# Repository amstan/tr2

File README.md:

# tr2

## Overview

The goal of this project is to develop a hardware and accompanying software
platform for controlling robots from a high level programming language such as
Python.

## Hardware

The hardware will consist of a multi-axis motor control board, industrial
strength GPIO for controlling alarms, incandescent lamps, driving fans and more.

## Software

The software will provide an abstract interface to the hardware platform. The
first robot that will be tailored to this project will be a 3-axis Delta Robot.

## Project Structure

Here is the folder structure for the project:

* blender/
    * 3D models of target robots
* board/
    * The first hardware platform for this project
* board/bomParser/
    * Some pretty untested code to do mass changes in schematics/BOMs
* datasheets/
    * Component datasheets
* doc/
    * Notes, logo
* firmware/
    * Bare metal bring up of STM32F4 and code for the robot controller
* pictures/
    * Various pictures of the project
* python/
    * The python software interfaces
* ui/
    * A user interface to all of this

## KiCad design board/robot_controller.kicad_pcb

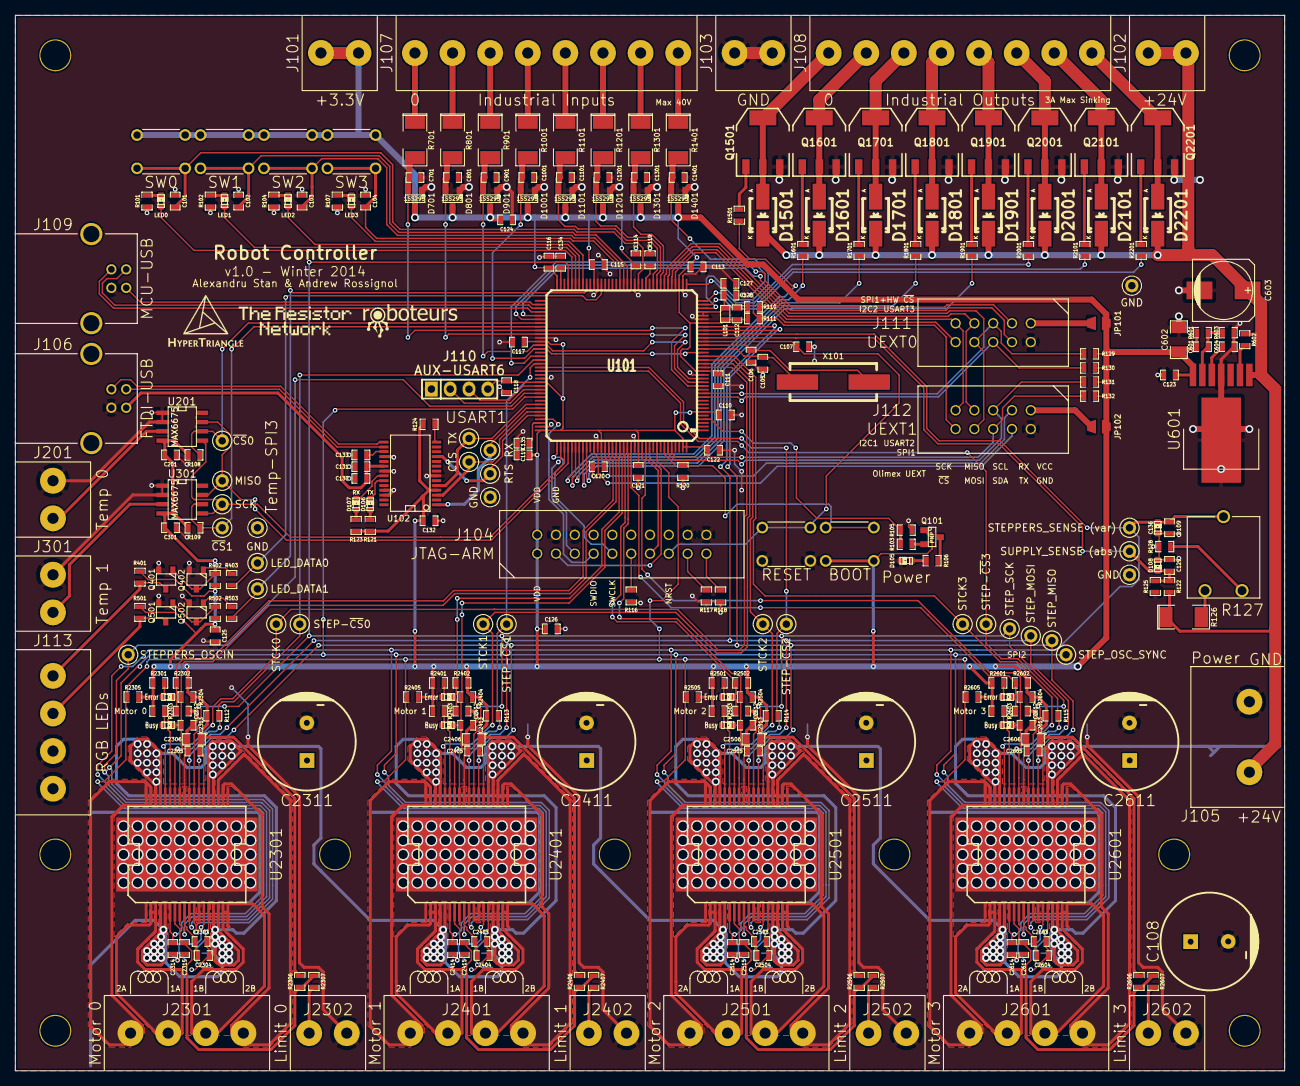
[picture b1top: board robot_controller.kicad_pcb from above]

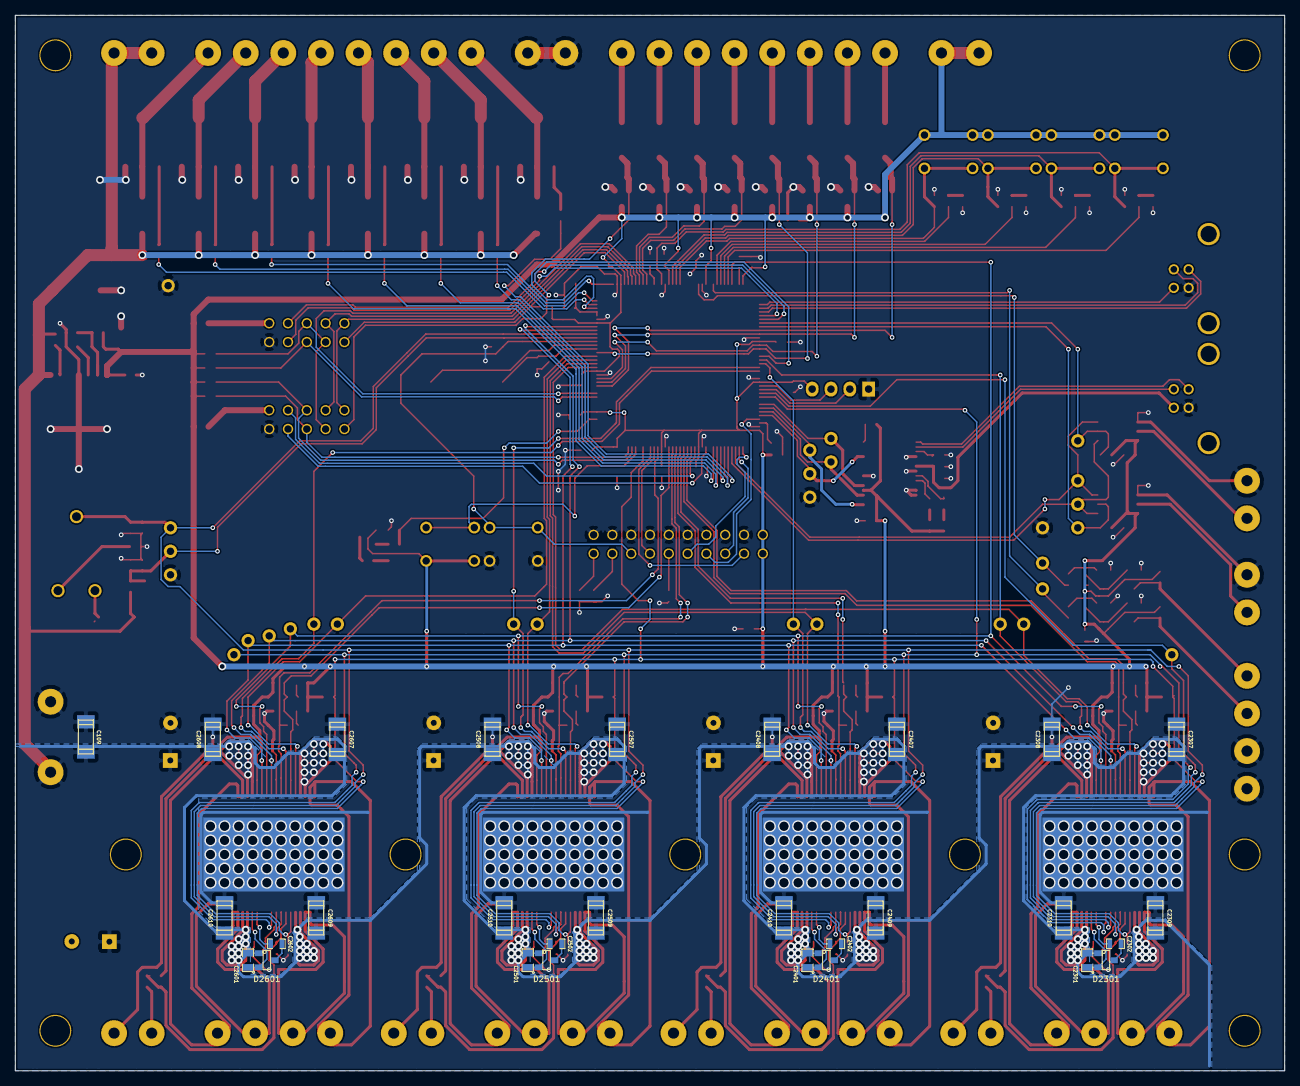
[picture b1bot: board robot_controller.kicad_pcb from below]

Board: 2 copper layers, 171.4 x 142.6 mm, 325 parts (29 on the bottom side), 199 nets.

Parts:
C101, C102, C103, C104, C2304, C2404, C2504, C2604: 10uF; SM0603_Capa
C105, C106: 18pF; SM0603_Capa
C107, C110, C111, C112, C113, C114, C115, C116, C117, C118, C119, C120, C121, C122, C123, C124, C125, C126, C129, C131, C132, C133, C201, C301, C2303, C2305, C2315, C2403, C2405, C2415, C2503, C2505, C2515, C2603, C2605, C2615: 100nF; SM0603_Capa
C108, C2311, C2411, C2511, C2611: 100uF; CP_13x21mm
C109, C2307, C2308, C2309, C2310, C2407, C2408, C2409, C2410, C2507, C2508, C2509, C2510, C2607, C2608, C2609, C2610: 100nF; c_1808
C127: 1uF; SM0603_Capa
C128, C2302, C2402, C2502, C2602: 10nF; SM0603_Capa
C130: 4.7uF; SM0603_Capa
C134, C135: 2.2uF; SM0603_Capa
C136: 33nF; SM0603_Capa
C601, C604: 22nF; SM0603_Capa
C602: 100uF; SM1206
C603: 10uF; c_elec_8x10
C701, C801, C901, C1001, C1101, C1201, C1301, C1401: 1nF; SM0603_Capa
C2301, C2401, C2501, C2601: 220nF; SM0805
C2306, C2406, C2506, C2606: 47uF; SM0805
C2312, C2313, C2314, C2412, C2413, C2414, C2512, C2513, C2514, C2612, C2613, C2614: 100pF; SM0603_Capa
D101: LED0; LED-0603
D102: LED1; LED-0603
D103: LED2; LED-0603
D104: LED3; LED-0603
D105: Power; LED-0603
D106: TX; LED-0603
D107: RX; LED-0603
D108, D109: 3.3V; LED-0603
D701, D801, D901, D1001, D1101, D1201, D1301, D1401: 1SS295; SOT23-EXTRASPECIAL
D1501, D1601, D1701, D1801, D1901, D2001, D2101, D2201: RSX501L-20TE25; Diode-SMA_Handsoldering
D2301, D2401, D2501, D2601: DOUBLE_SCHOTTKY; SOT23-SPECIAL
D2302, D2402, D2502, D2602: Error; LED-0603
D2303, D2403, D2503, D2603: Busy; LED-0603
J101: +3.3V; SCONN_2
J102: +24V; SCONN_2
J103: GND; SCONN_2
J104: JTAG-ARM; SHROUDED_20
J105: Power; PWRSCONN_2
J106: FTDI-USB; USB_B
J107: Industrial Inputs; SCONN_8
J108: Industrial Outputs; SCONN_8
J109: MCU-USB; USB_B
J110: AUX-USART6; Pin_Header_Straight_1x04
J111: UEXT0; SHROUDED_10
J112: UEXT1; SHROUDED_10
J113: RGB LEDs; SCONN_4
J201: Temp 0; SCONN_2
J301: Temp 1; SCONN_2
J2301: Motor 0; CONN_STEPPER
J2302: Limit 0; SCONN_2
J2401: Motor 1; CONN_STEPPER
J2402: Limit 1; SCONN_2
J2501: Motor 2; CONN_STEPPER
J2502: Limit 2; SCONN_2
J2601: Motor 3; CONN_STEPPER
J2602: Limit 3; SCONN_2
JP101, JP102: JUMPER; SOLDER_BRIDGE
L101: 100uH; SM0603
MH: MountingHole_2-5mm_RevA_Date21Jun2010; MountingHole_4mm
MH#2, MH#3, MH#4, MH#5, MH#6, MH#7, MH#8, MH#9: MountingHole_2-5mm_RevA_Date21Jun2010; MountingHole_4mm
Q101: PNP; SOT23-EXTRASPECIAL
Q401, Q402, Q501, Q502: MMBT5962; SOT23_INV
Q1501, Q1601, Q1701, Q1801, Q1901, Q2001, Q2101, Q2201: NJT4031NT1G; SOT223-EXTRASPECIAL
R101, R102, R104, R106, R107, R2307, R2407, R2507, R2607: 100; SM0603_Resistor
R103, R105, R402, R403, R502, R503: 1k; SM0603_Resistor
R108, R109, R110, R111, R112, R113, R114, R115, R116, R117, R118, R119, R120, R124, R2306, R2406, R2506, R2606: 10k; SM0603_Resistor
R121, R2303, R2403, R2503, R2603: 220; SM0603_Resistor
R122: 15k; SM0603_Resistor
R123, R2301, R2401, R2501, R2601: 316; SM0603_Resistor
R125, R603: 1.1k; SM0603_Resistor
R126, R701, R801, R901, R1001, R1101, R1201, R1301, R1401: 3.3k; SM2010
R127: 22k; TRIMMER_POT
R128: 820; SM0603_Resistor
R129, R130, R131, R132: 4.7k; SM0603_Resistor
R401, R501: 200; SM0603_Resistor
R601: 3.3k; SM0603_Resistor
R602: 62k; SM0603_Resistor
R1501, R1601, R1701, R1801, R1901, R2001, R2101, R2201: 470; SM0603_Resistor
R2302, R2304, R2305, R2402, R2404, R2405, R2502, R2504, R2505, R2602, R2604, R2605: 39k; SM0603_Resistor
SW101: SW0; PB
SW102: SW1; PB
SW103: SW2; PB
SW104: SW3; PB
SW105: RESET; PB
SW106: BOOT; PB
TP101: STEP_SCK; MINI_TP
TP102: STEP_MOSI; MINI_TP
TP103: STEP_MISO; MINI_TP
TP104: STEP-~{CS}0; MINI_TP
TP105: STEP-~{CS}1; MINI_TP
TP106: STEP-~{CS}2; MINI_TP
TP107: STEP-~{CS}3; MINI_TP
TP108: STCK0; MINI_TP
TP109: STCK1; MINI_TP
TP110: STCK2; MINI_TP
TP111: STCK3; MINI_TP
TP112: STEPPERS_OSCIN; MINI_TP
TP113: STEP_OSC_SYNC; MINI_TP
TP114, TP115, TP116, TP117: GND; MINI_TP
TP118: RX; MINI_TP
TP119: TX; MINI_TP
TP120: CTS; MINI_TP
TP121: RTS; MINI_TP
TP122: LED_DATA0; MINI_TP
TP123: LED_DATA1; MINI_TP
TP124: MISO; MINI_TP
TP125: SCK; MINI_TP
TP126: ~{CS}0; MINI_TP
TP127: ~{CS}1; MINI_TP
TP128: SUPPLY_SENSE (abs); MINI_TP
TP129: STEPPERS_SENSE (var); MINI_TP
U101: STM32F405-144; TQFP144
U102: FT232RL; SSOP-28
U201, U301: MAX6675; SOIC-8_N
U601: LMZ14201; PFM7
U2301, U2401, U2501, U2601: L6470; POWERSO-36
X101: 8MHZ; Crystal_HC49-SD_SMD

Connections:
+3.3V: C110.1, C111.1, C112.1, C113.1, C114.1, C115.1, C116.1, C117.1, C118.1, C119.1, C120.1, C121.1, C122.1, C123.1, C124.1, C125.1, C126.1, C132.1, C201.1, C301.1, C601.1, C602.1, C2305.1, C2306.1, C2405.1, C2406.1, C2505.1, C2506.1, C2605.1, C2606.1, D701.3, D801.3, D901.3, D1001.3, D1101.3, D1201.3, D1301.3, D1401.3, J101.1, J101.2, J104.1, J104.2, J110.4, JP101.2, JP102.2, L101.1, Q101.1, R108.1, R109.1, R110.1, R111.1, R112.1, R113.1, R114.1, R115.1, R121.2, R123.2, R124.2, R129.1, R130.1, R131.1, R132.1, R401.1, R402.1, R501.1, R502.1, R601.1, R2301.1, R2302.1, R2303.1, R2304.1, R2305.1, R2306.1, R2401.1, R2402.1, R2403.1, R2404.1, R2405.1, R2406.1, R2501.1, R2502.1, R2503.1, R2504.1, R2505.1, R2506.1, R2601.1, R2602.1, R2603.1, R2604.1, R2605.1, R2606.1, SW101.1, SW102.1, SW103.1, SW104.1, SW106.2, U101.6, U101.17, U101.30, U101.39, U101.52, U101.62, U101.72, U101.84, U101.95, U101.108, U101.121, U101.131, U101.143, U101.144, U102.4, U201.4, U301.4, U601.7, U2301.24, U2401.24, U2501.24, U2601.24
+3.3VADC: C127.1, C128.1, L101.2, U101.32, U101.33
+5V: C130.1, C131.1, J106.1, U102.20
+24V: C108.1, C109.1, C603.1, C2301.2, C2307.1, C2308.1, C2309.1, C2310.1, C2311.1, C2401.2, C2407.1, C2408.1, C2409.1, C2410.1, C2411.1, C2501.2, C2507.1, C2508.1, C2509.1, C2510.1, C2511.1, C2601.2, C2607.1, C2608.1, C2609.1, C2610.1, C2611.1, D1501.2, D1601.2, D1701.2, D1801.2, D1901.2, D2001.2, D2101.2, D2201.2, D2301.1, D2401.1, D2501.1, D2601.1, J102.1, J102.2, J105.1, R122.1, R126.1, R602.1, U601.1, U2301.4, U2301.5, U2301.15, U2301.16, U2301.22, U2301.23, U2301.33, U2301.34, U2401.4, U2401.5, U2401.15, U2401.16, U2401.22, U2401.23, U2401.33, U2401.34, U2501.4, U2501.5, U2501.15, U2501.16, U2501.22, U2501.23, U2501.33, U2501.34, U2601.4, U2601.5, U2601.15, U2601.16, U2601.22, U2601.23, U2601.33, U2601.34
/BOOT0: R120.1, SW106.1, U101.138
/BOOT1: R119.1, U101.48
/I2C1_SCL: J112.5, R131.2, U101.139
/I2C1_SDA: J112.6, R132.2, U101.140
/I2C2_SCL: J111.5, R129.2, U101.11
/I2C2_SDA: J111.6, R130.2, U101.10
/Industrial Input 0/A/D_Input: J107.1, R701.1
/Industrial Input 0/MCU_Input: C701.1, D701.2, R701.2, U101.13, U101.81
/Industrial Input 1/A/D_Input: J107.2, R801.1
/Industrial Input 1/MCU_Input: C801.1, D801.2, R801.2, U101.14, U101.82
/Industrial Input 2/A/D_Input: J107.3, R901.1
/Industrial Input 2/MCU_Input: C901.1, D901.2, R901.2, U101.15, U101.85
/Industrial Input 3/A/D_Input: J107.4, R1001.1
/Industrial Input 3/MCU_Input: C1001.1, D1001.2, R1001.2, U101.22, U101.86
/Industrial Input 4/A/D_Input: J107.5, R1101.1
/Industrial Input 4/MCU_Input: C1101.1, D1101.2, R1101.2, U101.46
/Industrial Input 5/A/D_Input: J107.6, R1201.1
/Industrial Input 5/MCU_Input: C1201.1, D1201.2, R1201.2, U101.45
/Industrial Input 6/A/D_Input: J107.7, R1301.1
/Industrial Input 6/MCU_Input: C1301.1, D1301.2, R1301.2, U101.44
/Industrial Input 7/A/D_Input: J107.8, R1401.1
/Industrial Input 7/MCU_Input: C1401.1, D1401.2, R1401.2, U101.34
/Industrial Output 0/MCU_Pin: R1501.1, U101.113
/Industrial Output 0/Sink: D1501.1, J108.1, Q1501.3
/Industrial Output 1/MCU_Pin: R1601.1, U101.114
/Industrial Output 1/Sink: D1601.1, J108.2, Q1601.3
/Industrial Output 2/MCU_Pin: R1701.1, U101.115
/Industrial Output 2/Sink: D1701.1, J108.3, Q1701.3
/Industrial Output 3/MCU_Pin: R1801.1, U101.116
/Industrial Output 3/Sink: D1801.1, J108.4, Q1801.3
/Industrial Output 4/MCU_Pin: R1901.1, U101.117
/Industrial Output 4/Sink: D1901.1, J108.5, Q1901.3
/Industrial Output 5/MCU_Pin: R2001.1, U101.37
/Industrial Output 5/Sink: D2001.1, J108.6, Q2001.3
/Industrial Output 6/MCU_Pin: R2101.1, U101.36
/Industrial Output 6/Sink: D2101.1, J108.7, Q2101.3
/Industrial Output 7/MCU_Pin: R2201.1, U101.35
/Industrial Output 7/Sink: D2201.1, J108.8, Q2201.3
/JTCK/SWCLK: J104.9, U101.109
/JTDI: J104.5, U101.110
/JTDO: J104.13, U101.133
/JTMS/SWDIO: J104.7, U101.105
/LED0: D101.1, U101.68
/LED1: D102.1, U101.67
/LED2: D103.1, U101.66
/LED3: D104.1, U101.65
/LED Data 0/DATA_IN: R403.2, TP122.1, U101.60
/LED Data 0/DATA_OUT: J113.1, Q401.3, R401.2
/LED Data 1/DATA_IN: R503.2, TP123.1, U101.64
/LED Data 1/DATA_OUT: J113.2, Q501.3, R501.2
/LED_PWR: R103.1, R105.2, U101.4
/MCU_RESET: C107.1, J104.15, SW105.1, U101.25
/NJTRST: J104.3, U101.134
/SPI1_MISO: J111.7, J112.7, U101.42
/SPI1_MOSI: J111.8, J112.8, U101.43
/SPI1_SCK: J111.9, J112.9, U101.41
/SUPPLY_SENSE: C129.1, D108.2, R122.2, R125.1, TP128.1, U101.26
/SW0: C101.1, SW101.2, U101.50
/SW1: C102.1, SW102.2, U101.53
/SW2: C103.1, SW103.2, U101.54
/SW3: C104.1, SW104.2, U101.55
/Stepper 0/ADCIN: C136.1, D109.2, R127.2, TP129.1, U101.27, U2301.8, U2401.8, U2501.8, U2601.8
/Stepper 0/OSCIN: TP112.1, U101.98, U2301.10
/Stepper 0/SCK: TP101.1, U101.69, U2301.26, U2401.26, U2501.26, U2601.26
/Stepper 0/SDI: TP102.1, U101.29, U2301.27, U2401.27, U2501.27, U2601.27
/Stepper 0/SDO: TP103.1, U101.28, U2301.25, U2401.25, U2501.25, U2601.25
/Stepper 0/STCK: TP108.1, U101.18, U2301.32
/Stepper 0/VREG: C2303.1, C2304.1, U2301.9
/Stepper 0/~BUSY/SYNC: C2313.1, D2303.2, R2304.2, U101.124, U2301.29
/Stepper 0/~CS: R112.2, TP104.1, U101.89, U2301.30
/Stepper 0/~FLAG: C2312.1, D2302.2, R2302.2, U101.123, U2301.31
/Stepper 0/~STBY/RST: C2314.1, C2414.1, C2514.1, C2614.1, R2305.2, R2405.2, R2505.2, R2605.2, U101.136, U2301.6, U2401.6, U2501.6, U2601.6
/Stepper 1/OSCIN: TP113.1, U101.99, U2301.11, U2401.10, U2501.10, U2601.10
/Stepper 1/STCK: TP109.1, U101.19, U2401.32
/Stepper 1/VREG: C2403.1, C2404.1, U2401.9
/Stepper 1/~BUSY/SYNC: C2413.1, D2403.2, R2404.2, U101.126, U2401.29
/Stepper 1/~CS: R113.2, TP105.1, U101.90, U2401.30
/Stepper 1/~FLAG: C2412.1, D2402.2, R2402.2, U101.125, U2401.31
/Stepper 2/STCK: TP110.1, U101.20, U2501.32
/Stepper 2/VREG: C2503.1, C2504.1, U2501.9
/Stepper 2/~BUSY/SYNC: C2513.1, D2503.2, R2504.2, U101.128, U2501.29
/Stepper 2/~CS: R114.2, TP106.1, U101.91, U2501.30
/Stepper 2/~FLAG: C2512.1, D2502.2, R2502.2, U101.127, U2501.31
/Stepper 3/STCK: TP111.1, U101.21, U2601.32
/Stepper 3/VREG: C2603.1, C2604.1, U2601.9
/Stepper 3/~BUSY/SYNC: C2613.1, D2603.2, R2604.2, U101.132, U2601.29
/Stepper 3/~CS: R115.2, TP107.1, U101.92, U2601.30
/Stepper 3/~FLAG: C2612.1, D2602.2, R2602.2, U101.129, U2601.31
/Temp Sensor 0/SCK: TP125.1, U101.111, U201.5, U301.5
/Temp Sensor 0/SO: TP124.1, U101.112, U201.7, U301.7
/Temp Sensor 0/~CS: R108.2, TP126.1, U101.79, U201.6
/Temp Sensor 1/~CS: R109.2, TP127.1, U101.80, U301.6
/UEXT0_~CS: J111.10, R110.2, U101.40
/UEXT1_~CS: J112.10, R111.2, U101.88
/USART1_CTS: TP120.1, U101.103, U102.3
/USART1_RTS: TP121.1, U101.104, U102.11
/USART1_RX: TP118.1, U101.102, U102.1
/USART1_TX: TP119.1, U101.101, U102.5
/USART2_RX: J112.3, U101.122
/USART2_TX: J112.4, U101.119
/USART3_RX: J111.3, U101.78
/USART3_TX: J111.4, U101.77
/USART6_RX: J110.2, U101.97
/USART6_TX: J110.3, U101.96
/USB_DM: J109.2, U101.75
/USB_DP: J109.3, U101.76
/USB_VBUS: J109.1, U101.74
/VCAP1: C134.1, U101.71
/VCAP2: C135.1, U101.106
/XTAL_IN: C105.1, U101.23, X101.1
/XTAL_OUT: C106.1, U101.24, X101.2
GND: C101.2, C102.2, C103.2, C104.2, C105.2, C106.2, C107.2, C108.2, C109.2, C110.2, C111.2, C112.2, C113.2, C114.2, C115.2, C116.2, C117.2, C118.2, C119.2, C120.2, C121.2, C122.2, C123.2, C124.2, C125.2, C126.2, C127.2, C128.2, C129.2, C130.2, C131.2, C132.2, C133.2, C134.2, C135.2, C136.2, C201.2, C301.2, C602.2, C603.2, C604.2, C701.2, C801.2, C901.2, C1001.2, C1101.2, C1201.2, C1301.2, C1401.2, C2303.2, C2304.2, C2305.2, C2306.2, C2307.2, C2308.2, C2309.2, C2310.2, C2311.2, C2312.2, C2313.2, C2314.2, C2315.2, C2403.2, C2404.2, C2405.2, C2406.2, C2407.2, C2408.2, C2409.2, C2410.2, C2411.2, C2412.2, C2413.2, C2414.2, C2415.2, C2503.2, C2504.2, C2505.2, C2506.2, C2507.2, C2508.2, C2509.2, C2510.2, C2511.2, C2512.2, C2513.2, C2514.2, C2515.2, C2603.2, C2604.2, C2605.2, C2606.2, C2607.2, C2608.2, C2609.2, C2610.2, C2611.2, C2612.2, C2613.2, C2614.2, C2615.2, D105.2, D108.1, D109.1, D701.1, D801.1, D901.1, D1001.1, D1101.1, D1201.1, D1301.1, D1401.1, J103.1, J103.2, J104.4, J104.6, J104.8, J104.10, J104.12, J104.14, J104.16, J104.18, J104.20, J105.2, J106.4, J109.4, J110.1, J111.2, J112.2, J113.3, J113.4, J201.1, J301.1, J2302.2, J2402.2, J2502.2, J2602.2, Q401.1, Q402.1, Q501.1, Q502.1, Q1501.1, Q1601.1, Q1701.1, Q1801.1, Q1901.1, Q2001.1, Q2101.1, Q2201.1, R101.2, R102.2, R104.2, R105.1, R107.2, R116.2, R117.2, R118.2, R119.2, R120.2, R125.2, R128.2, R603.2, SW105.2, TP114.1, TP115.1, TP116.1, TP117.1, U101.16, U101.31, U101.38, U101.51, U101.61, U101.83, U101.94, U101.107, U101.120, U101.130, U102.7, U102.18, U102.21, U102.25, U102.26, U201.1, U201.2, U301.1, U301.2, U601.4, U2301.1, U2301.12, U2301.19, U2301.28, U2301.PAD, U2401.1, U2401.12, U2401.19, U2401.28, U2401.PAD, U2501.1, U2501.12, U2501.19, U2501.28, U2501.PAD, U2601.1, U2601.12, U2601.19, U2601.28, U2601.PAD
unnamed: C133.1, U102.17
unnamed: C601.2, R601.2, R603.1, U601.6
unnamed: C604.1, U601.5
unnamed: C2301.1, D2301.3, U2301.14
unnamed: C2302.1, D2301.2
unnamed: C2302.2, U2301.13
unnamed: C2315.1, R2306.2, R2307.2, U2301.7
unnamed: C2401.1, D2401.3, U2401.14
unnamed: C2402.1, D2401.2
unnamed: C2402.2, U2401.13
unnamed: C2415.1, R2406.2, R2407.2, U2401.7
unnamed: C2501.1, D2501.3, U2501.14
unnamed: C2502.1, D2501.2
unnamed: C2502.2, U2501.13
unnamed: C2515.1, R2506.2, R2507.2, U2501.7
unnamed: C2601.1, D2601.3, U2601.14
unnamed: C2602.1, D2601.2
unnamed: C2602.2, U2601.13
unnamed: C2615.1, R2606.2, R2607.2, U2601.7
unnamed: D101.2, R101.1
unnamed: D102.2, R102.1
unnamed: D103.2, R104.1
unnamed: D104.2, R107.1
unnamed: D105.1, R106.1
unnamed: D106.1, R121.1
unnamed: D106.2, U102.23
unnamed: D107.1, R123.1
unnamed: D107.2, U102.22
unnamed: D2302.1, R2301.2
unnamed: D2303.1, R2303.2
unnamed: D2402.1, R2401.2
unnamed: D2403.1, R2403.2
unnamed: D2502.1, R2501.2
unnamed: D2503.1, R2503.2
unnamed: D2602.1, R2601.2
unnamed: D2603.1, R2603.2
unnamed: J104.11, R116.1
unnamed: J104.17, R117.1
unnamed: J104.19, R118.1
unnamed: J106.2, U102.16
unnamed: J106.3, U102.15
unnamed: J111.1, JP101.1
unnamed: J112.1, JP102.1
unnamed: J201.2, U201.3
unnamed: J301.2, U301.3
unnamed: J2301.1, U2301.35, U2301.36
unnamed: J2301.2, U2301.2, U2301.3
unnamed: J2301.3, U2301.17, U2301.18
unnamed: J2301.4, U2301.20, U2301.21
unnamed: J2302.1, R2307.1
unnamed: J2401.1, U2401.35, U2401.36
unnamed: J2401.2, U2401.2, U2401.3
unnamed: J2401.3, U2401.17, U2401.18
unnamed: J2401.4, U2401.20, U2401.21
unnamed: J2402.1, R2407.1
unnamed: J2501.1, U2501.35, U2501.36
unnamed: J2501.2, U2501.2, U2501.3
unnamed: J2501.3, U2501.17, U2501.18
unnamed: J2501.4, U2501.20, U2501.21
unnamed: J2502.1, R2507.1
unnamed: J2601.1, U2601.35, U2601.36
unnamed: J2601.2, U2601.2, U2601.3
unnamed: J2601.3, U2601.17, U2601.18
unnamed: J2601.4, U2601.20, U2601.21
unnamed: J2602.1, R2607.1
unnamed: Q101.2, R103.2
unnamed: Q101.3, R106.2
unnamed: Q401.2, Q402.3, R402.2
unnamed: Q402.2, R403.1
unnamed: Q501.2, Q502.3, R502.2
unnamed: Q502.2, R503.1
unnamed: Q1501.2, R1501.2
unnamed: Q1601.2, R1601.2
unnamed: Q1701.2, R1701.2
unnamed: Q1801.2, R1801.2
unnamed: Q1901.2, R1901.2
unnamed: Q2001.2, R2001.2
unnamed: Q2101.2, R2101.2
unnamed: Q2201.2, R2201.2
unnamed: R124.1, U102.14
unnamed: R126.2, R127.1
unnamed: R127.3, R128.1
unnamed: R602.2, U601.2

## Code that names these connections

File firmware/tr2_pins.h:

#pragma once

#define _JOINPIN(port, pin) port##_##pin

// USB
#define USB_VBUS PB13
#define USB_DM   PB14 // not a bootloader D:
#define USB_DP   PB15

// FTDI
#define FTDI_USART(x) _JOINPIN(USART1, x) // + bootloader
#define USART1_TX  PA9
#define USART1_RX  PA10
#define USART1_CTS PA11
#define USART1_RTS PA12

// AUX_UART
#define AUX_USART(x) _JOINPIN(USART6, x)
#define USART6_TX PC6
#define USART6_RX PC7

// UEXT0
#define UEXT0_USART(x) _JOINPIN(USART3, x)
#define USART3_TX PD8
#define USART3_RX PD9

#define UEXT0_I2C(x) _JOINPIN(I2C2, x) // 4.7k pullups
#define I2C2_SDA  PF0
#define I2C2_SCL  PF1

#define UEXT0_SPI(x) _JOINPIN(SPI1, x) // Same as UEXT1
#define UEXT0_CS  PA4

// UEXT1
#define UEXT1_USART(x) _JOINPIN(USART2, x)
#define USART2_TX PD5
#define USART2_RX PD6

#define UEXT1_I2C(x) _JOINPIN(I2C1, x) // 4.7k pullups
#define I2C1_SDA  PB9
#define I2C1_SCL  PB8

#define UEXT1_SPI(x) _JOINPIN(SPI1, x) // Same as UEXT0
#define UEXT1_CS  PA4

#define SPI1_MOSI PA7
#define SPI1_MISO PA6
#define SPI1_SCK  PA5

// Misc
#define BOOT1 PB2 // 10k ext pulldown

#define NJTRST PB4
#define JTDI   PA15
#define JTMS   PA13
#define JTCK   PA14
#define JTDO   PB3

#define XTAL_IN  PH0
#define XTAL_OUT PH1

// RGB LED connectors
#define LED_DATA0 PE9
#define LED_DATA1 PE11
// Note: need rework to bypass broken "booster"

// Board LEDs
#define LED_PWR PE5 // Active low, HiZ also means on

#define LED0 PE15 // Active high
#define LED1 PE14
#define LED2 PE13
#define LED3 PE12

// Board Buttons, 10uF, need software pulldowns
#define SW0 PF12
#define SW1 PF13
#define SW2 PF14
#define SW3 PF15

// Analog
#define SUPPLY_SENSE   PC0 // ADC123_IN10, 1.1k / (1.1k + 15k) * 24V
#define STEPPERS_SENSE PC1 // ADC123,IN11, Settable potentiometer, ideally at 0.5 * 3.3V, goes to ADCIN on L6470

// Industrial Inputs
// 48kHz Single Pole Low Pass Filter (3.3k, 1nF)
// 0.7mA @ 24V Input, 210mV drop on Schottky array
// Max 40V
#define IND_INPUT0 PF3  // ADC3_IN9
#define IND_INPUT1 PF4  // ADC3_IN14
#define IND_INPUT2 PF5  // ADC3_IN15
#define IND_INPUT3 PF10 // ADC3_IN8
#define IND_INPUT4 PB0  // ADC12_IN8
#define IND_INPUT5 PC5  // ADC12_IN15
#define IND_INPUT6 PC4  // ADC12_IN14
#define IND_INPUT7 PA0  // ADC123_IN0
#define IND_INPUT0_TIM PD12
#define IND_INPUT1_TIM PD13
#define IND_INPUT2_TIM PD14
#define IND_INPUT3_TIM PD15

// Industrial Outputs
// 3A Max Sinking
// NJT4031NT1G NPN transistors + flyback diodes to 24V
#define IND_OUTPUT0 PC12
#define IND_OUTPUT1 PD0
#define IND_OUTPUT2 PD1
#define IND_OUTPUT3 PD2
#define IND_OUTPUT4 PD3
#define IND_OUTPUT5 PA3
#define IND_OUTPUT6 PA2
#define IND_OUTPUT7 PA1

// MAX6675
#define TEMP_SPI(x)  _JOINPIN(SPI3, x)
#define SPI3_MISO PC11
#define SPI3_SCK  PC10
#define TEMP0_CS  PD10
#define TEMP1_CS  PD11

// L6470 Steppers
#define STEPPERS_RST      PB6
#define STEPPERS_OSCIN    PC8
#define STEPPERS_OSC_SYNC PC9

#define STEPPERS_SPI(x) _JOINPIN(SPI2, x)
#define SPI2_MOSI PC3
#define SPI2_MISO PC2
#define SPI2_SCK  PB10

#define STEPPER0_CS PG4
#define STEPPER1_CS PG5
#define STEPPER2_CS PG6
#define STEPPER3_CS PG7

#define STEPPER0_STCK PF6
#define STEPPER1_STCK PF7
#define STEPPER2_STCK PF8
#define STEPPER3_STCK PF9

#define STEPPER0_FLAG PD7 // Error when low
#define STEPPER1_FLAG PG10
#define STEPPER2_FLAG PG12
#define STEPPER3_FLAG PG14

#define STEPPER0_BUSY PG9 // !BUSY/FLAG
#define STEPPER1_BUSY PG11
#define STEPPER2_BUSY PG13
#define STEPPER3_BUSY PG15

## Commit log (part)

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2013-10-02 Initial commit: readme and python gitignore
2013-10-03 added folders
2013-10-03 start of kinematics code: some forward kinematics math
2013-10-05 rotated blender model so it matches the code
2013-10-05 Got blender to do live inverse kinematics using our code. Changed to the right point for the circle intersect
2013-10-06 fixed forward kinematics(i had the radius wrong), blender can now do forward kinematics too
2013-10-06 Tried to see how the the resolution distribution looks like.
2013-12-09 Updated README, Renamed board-1 folder
    I have updated the README file to contain a bit more details about the
    project. I have renamed the pcb/ folder to board-1/. I anticipate that
    this project could support multiple hardware platforms.
2013-12-11 organized python folder
2014-01-05 added a virtual stepper driver attempt
2014-01-05 finally made the stepper code compatible with python3, freaking bytes and unicode!
2014-01-14 stops in time now, for all positive cases!
2014-01-14 perfect moving
2014-01-21 Created a KiCAD project
    This commit brings in a KiCAD project that is empty. I am preparing to
    build the latest version of KiCAD.
2014-01-22 organized datasheets in their own folders
2014-01-22 Created STM32F405-144 Component in Project Library
2014-01-25 Added Stepper Motor Driver(L670)
2014-01-25 Added watercooling drawing
2014-01-26 Added MAX6675 symbol to the components library. Fixed pins on L6470.
2014-01-27 Voltage Regulator, Reset Logic
2014-01-27 Added schematic for the temperature amplifier. Removed useless NC pin.
2014-01-27 Wired up the stepper driver blocks in the main schematic.
2014-01-27 Fixed airwire positions.
2014-01-27 Industrial Input
    I have designed an industrial input that is low-pass filtered and
    schottky diode protected against over and under voltage. This circuit
    will work for both analog and digital.
2014-01-27 Industrial Input Schematic Notes
2014-01-29 Worked on the stepper motor interface.
    * Organized stepper files better(moved buspirate driver in another file).
    * Added check for the status register(with exceptions!).
    * Tried the bigger motor(no OCD problems this time!).
2014-01-30 Played some more with the servo settings.
    I can now run the servo at almost the full speed allowed by the driver(1048575).
    At this speed the motor uses almost the full 3A.
2014-02-01 Robot Controller Boot Logic, Decoupling
    I have added boot logic to the main schematic that will allow us to
    boot from the serial bootloader by pressing a button on the board.
    I have added decoupling to the base MCU for analog and digital.
2014-02-01 Hardware USB
    I have added hardware USB support to the board.
2014-02-01 SPI for Steppers and Temperature
    I cleaned up the stepper driver section of the main schematic and
    routed the high speed SPI interface over to it. I also got the second
    SPI module connected to the temperature sensors.
2014-02-01 Added JTAG Debug Port
    I have added the JTAG debug port. The JTAG lines are internally pulled
    high by the MCU to avoid an unknown JTAG state.
2014-02-02 switched to pirate430 driver, added some safety when resetting
2014-02-02 Removed double schottky
    The double schottky wouldn't do much in this case. I have removed it.
2014-02-06 Schematic Additions
    * UEXT
    * AUX UART
    * Regulator
    * Fixed hirearchical label directions
2014-02-06 Decoupled analog section with an inductor.
2014-02-06 Replaces the 2 diodes with a double shottky diode for the steppers.
2014-02-06 Connected USB VBUS to the right MCU pin.
2014-02-06 Connected the UEXT UARTS/I2C/SPI in the right places
2014-02-07 Created Firmware README
2014-02-08 OpenOCD in the Makefile, Simple main program!
    I got OpenOCD going in the Makefile and wrote a simple while(1) test program. I
    was able to load it using gdb 'load'. Woo!
2014-02-08 Default interrupt handler
    Added a default interrupt handler. The chip just goes into it, I need
    to figure that out.
2014-02-08 Blue LED!
    This commit enables the blue LED on the STM32F4DISCOVERY board.
2014-02-08 Simplistic Reset/Clock, Gpio Drivers
    This commit brings in the foundation for a driver for the reset/clock
    logic and gpio peripherals.
2014-02-09 GPIO Headers Complete
    I have finished the GPIO header file. It would be nice to write some
    driver functions, but this is good enough for now.
2014-02-09 GPIO Headers, Peripherals Added to Clock Driver
    I have mostly completed the GPIO headers. I have added the remaining
    peripherals to the SystemResetClock header. I think it is time for an
    SPI driver.
2014-02-09 Things are getting a little volatile!
    Silly me.. forgot to make struct instances volatile. Compiler
    optimizations were sure to break my sample programs.
2014-02-10 Reiner Documentation, Industrial GPIO, Driver Fix
    I added documentation for the meaning of Reiner's board pins. I have
    finished implemented the industrial inputs on the schematic and partial
    industrial outputs. I have added some capacitors to the motor drivers.
2014-02-10 GPIO Update, Spi Update, Uart Started
    I have changed GPIO to be a struct of GPIO modules, removed the enum
    of SPI modules and started working on the UART.
2014-02-12 Made a more efficient use of the MCU hardware peripherals.
    See https://github.com/amstan/tr2/wiki/MCU-Pheripherals-Allocation for more details.
    * Added STCK pins to individual timers so the MCU can control the steppers step by step.
    * Worried about the Industrial GPIOs to be connected to timers(most of them)
    * Swapped some SPIs and UARTs to achieve better speeds
    * Cleaned up schematic
2014-02-13 Added fp-lib-table and a library with an existing stepper motor package
2014-02-15 UART Working, Interrupts
    UART is now working, I am able to transmit bytes. I have wrote a header
    file for the NVIC in the Cortex-M4 core. It needs a bit of work, but I
    am able to enable the UART interrupt and execute it.
2014-02-15 Added POWERSO-36 footprint
2014-02-16 Added test points to the schematic.
2014-02-16 Comprehensive Schematic Review, Power LED
    The schematic was reviewed. Components were selected. Fixed minor bugs
    encountered during review. Debounced switches.
    Added a power LED with a transistor that causes it to be normally-on.
2014-02-16 Fixed ERC Errors. Annotated all components.
2014-02-16 GDB Init, Interrupts, Start Code in C, UART Start
    * Created a GDB init file that automatically connects to OpenOCD
    and reset/halts the processor
    * Wrote a header file for the NVIC in the M4
    * Changed start code to C, found some bugs in the asm version (I suck
    at assembly).
    * Started working on an interrupt driven UART driver
2014-02-16 Renamed Registers to enumerated types
    I have renamed the register bit names to enumerated types if
    applicable. This makes debugging a bit nicer.
2014-02-16 Interrupt Driven Tx and Rx
    I have interrupt driven, non-blocking Tx and Rx working now. I need to
    concern myself with thread safety now before saying this is complete.
2014-02-17 Selected Part Numbers for all Components
2014-02-17 Thread Safety Bug Fixes
    I have made the driver thread-safe by disabling Tx/Rx interrupts when
    accessing the Tx and Rx buffers.
2014-02-17 Industrial Output Ground, Associated Footprints
    * Fixed an issue with the industrial output ground, it is now on the
    power ground rail.
    * Associated most of the footprints, need to make a few.
2014-02-17 Resolved issues while associating footprints.
2014-02-17 Pin/Port GPIO Definitions, Typedef'd GPIO Structs
2014-02-17 Added a Pins Enum, Changed Sample Program to Echo
2014-02-17 Digikey Link Adder
    I have created a utility to interactively add Digikey part numbers and
    links to our schematics. This will help a lot when creating footprints
    and placing orders.
2014-02-17 Minor tweaks to the Digikey Link Adder Regex
2014-02-17 Created Stepper Driver Footprint, FreeCAD Test
    I created a stepper driver footprint.
    I also experimented with FreeCAD in the models folder. It might be nice
    to create 3D models of our components.
2014-02-17 Renamed Clocks
    I renamed the clock define.
2014-02-18 Prepared components/footprints for PCB Layout.
2014-02-19 Worked a little on the PCB layout.
2014-02-20 Worked on the stepper layout
2014-02-28 PFM7 Footprint
    Created a footprint for the TI PFM7 package. Used for the main 3.3V
    switching regulator.
2014-02-28 SOT223 Extra Special
    Created SOT223 package for the industrial output transistors.
2014-02-28 Added vias of proper sizes for 24V near the stepper drivers
2014-03-01 Worked on a way to route the 5 wires underneath the capacitor.
2014-03-01 SCONN_8 Footprint
    Created SCONN_8 footprint for the industrial GPIO.
2014-03-01 Started layout of a few other 'modules'. More work on the stepper drivers. Used more Andrew footprints.
2014-03-01 USB_B Footprint
    Created a USB-B connector footprint.
2014-03-02 TRIMMER_POT Footprint
    Created a trim pot footprint.
2014-03-02 Layed out in general where stuff is going to be located.
2014-03-02 Organized MCU components in the layout
2014-03-02 MINI_TP Footprint
    Created a footprint for the test points used in our project.
2014-03-02 Added pushbuttons to the PCB Layout
2014-03-02 SOLDER_BRIDGE Footprint
    Added the SOLDER_BRIDGE footprint to our component library. I added it
    to the layout as well.
2014-03-02 Named all connectors/leds/switches based on their functionality, refdes's are safe.
2014-03-02 Copied stepper layouts, no extra parts were found :)
2014-03-03 Added more zones. Started routing traces from stepper motors
2014-03-08 Started layout on the mcu.
2014-03-10 More pcb layout
2014-03-10 No more airwires
2014-03-10 Board pretty much done.
2014-03-10 Fixed Main Power Footprint
    Updated the footprint on the PCB layout and the track connected to it.
2014-03-10 moved board to fit in the page
2014-03-10 Fixed hole size on shrouded connectors
2014-03-10 Increased the size of the PFM heatsink.
    Solder can be applied from the top now, hopefully avoiding an oven.
2014-03-10 Fixed DRC with the new part changes
2014-03-11 More silkscreen changes, more track fiddling.
2014-03-11 PentaLogix DRC Fixes
    Moved some traces inside of the board outline.
2014-03-11 Fixed annular ring errors
2014-03-11 Removed soldermask from the bottom side of the board underneath the drivers.
2014-03-14 SPI WriteRead Function
2014-03-15 Initial UI Work
    Started creating a user interface.
2014-03-15 Pictures taken before PCB assembly
    Taken with a small USB microscope.
2014-03-15 Updated README, Started Protocol Definition
2014-03-15 User LED protocol definition
2014-03-24 Moved board stuff in the board folder
2014-03-25 Struct to Defines
    I changed from a struct with padding variables to multiple UART
    defines. The padding variables do not make much sense.
    Protocol definition is under way.
2014-03-26 Continued Protocol Definition
2014-03-27 Stepper Driver Improvements
    Added better exception handling.
    It now includes descriptions for the exceptions and __str__ and __repr__ methods.
    Added a wait method that blocks until it's not busy.
    Fixed issue with negative goto.
2014-03-27 Integrating kinematics
2014-03-27 Having difficulties with the dimensions of the robot, it i can't seem to get a straight line.
2014-03-28 Changed to real units for the speed functions in the Arm abstractions
2014-03-29 Have linear interpolation working
2014-03-29 Spi Write/Read Working and a Test case in C#
2014-03-29 Clock Control Register Defined
2014-03-29 Added sprogram target, commented PLL configuration
    I added an sprogram target to support loading code using the serial
    bootloader.
2014-03-29 Started work on a python protocol driver for the mcu
2014-03-30 Added CRC Validation to Protocol Commands
2014-03-30 Protocol implementations on the python side, includes KeyboardInterrupt handling.
2014-03-30 Minor change to CSharp test
2014-03-31 Added a read input command
2014-04-01 Adjusted WS2812 timings
2022-01-17 upgraded to kicad 6
2022-01-18 board: added pdf render for future viewing pleasure
